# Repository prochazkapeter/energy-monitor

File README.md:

# energy-monitor

Energy consumption monitoring device using NodeMCU-32S and PZEM-004T v 3.0 module over MQTT.
This device could be easily integrated to Home Assistant using Mosquitto broker add-on.
You could visualize the data using standard hassio tools or implement ingestion to InfluxDB and
use Grafana.

This repo also contains 3D model of custom enclosure, which was printed using Prusa Mini+.
The ESP32 dev kit is mounted on custom PCB with DC power supply from 230 V. The PCB schematics 
are located in em_schematic directory.

## Quick Start

- download firmware and power up the device
- device acts as an AP, connect to it via mobile phone
- fill in Wi-Fi credentials and MQTT broker details

### MQTT Topics
- device sends measurements in JSON format to **homeenergy/sensor1** (can be changed in config.h)
- device listens to commands on **esp32/sensor1**
- data format -> {"voltage":"231.1","current":"0.540","power":"92.100",
  "energy":"18.53","projection":"180640","frequency":"50.0","pfactor":"0.74"}
 
### MQTT Commands
- **on**/**off** -> control the blue LED on ESP32 dev kit
- **resetEnergy** -> reset energy counter
- **resetWiFi** -> reset WiFi credentials
- **restartESP** -> restart the device
- **datefrom-dd/mm/yy** -> set start of the billing period
- **billdate-dd/mm/yy** -> set end of the billing period

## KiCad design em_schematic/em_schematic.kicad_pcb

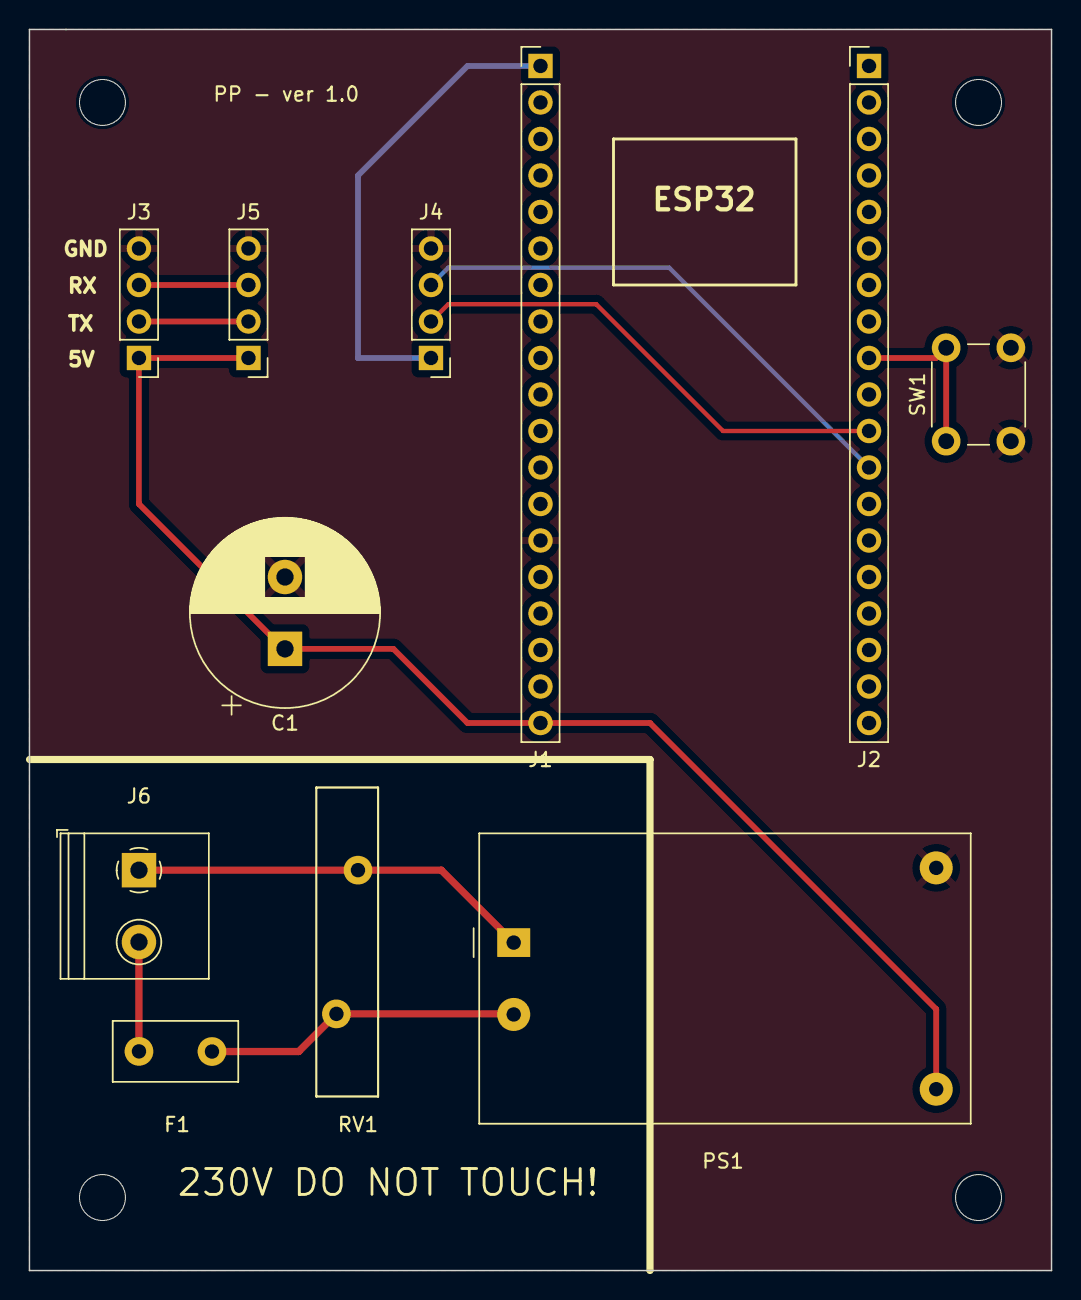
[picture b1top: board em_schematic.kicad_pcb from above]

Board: 2 copper layers, 71.1 x 86.4 mm, 11 parts (0 on the bottom side), 11 nets.

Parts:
C1: C_Polarized; CP_Radial_D13.0mm_P5.00mm
F1: Fuse; Fuse_Littelfuse_395Series
J1, J2: Conn_01x19; PinHeader_1x19_P2.54mm_Vertical
J3, J4, J5: Conn_01x04; PinHeader_1x04_P2.54mm_Vertical
J6: Screw_Terminal_01x02; TerminalBlock_Philmore_TB132_1x02_P5.00mm_Horizontal
PS1: HLK-PM01; Converter_ACDC_HiLink_HLK-PMxx
RV1: Varistor; RV_Disc_D21.5mm_W4.3mm_P10mm
SW1: SW_Push; SW_PUSH_6mm_H5mm

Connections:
+5V: C1.1, J1.19, J3.1, J5.1, PS1.4 (+Vout)
GND: C1.2, J1.14, J3.4, J4.4, J5.4, PS1.3 (-Vout), SW1.2
unnamed: J1.1, J4.1
unnamed: J2.9, SW1.1
unnamed: J2.11, J4.2
unnamed: J2.12, J4.3
unnamed: J3.2, J5.2
unnamed: J3.3, J5.3
unnamed: J6.1, PS1.1 (AC/L), RV1.1
unnamed: F1.1, J6.2
unnamed: F1.2, PS1.2 (AC/N), RV1.2

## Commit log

2022-12-26 Created functions for calibration and measurement of RMS Voltage
2023-02-24 measurement with pzem-004t, uploading to InfluxDB endpoint
2023-03-30 Implemented MQTT to Home Assistant
2023-04-12 working with dates
2023-04-12 edited config
2023-04-17 working with time, calculating projection
2023-05-11 WiFi provisioning
    Implemented Wi-Fi provisioning from phone and separated main file to measurement and network files
2023-05-17 KiCad schematic
2023-05-17 MQTT parameters now handed from phone
2023-05-22 added 3d files for prototype enclosure
